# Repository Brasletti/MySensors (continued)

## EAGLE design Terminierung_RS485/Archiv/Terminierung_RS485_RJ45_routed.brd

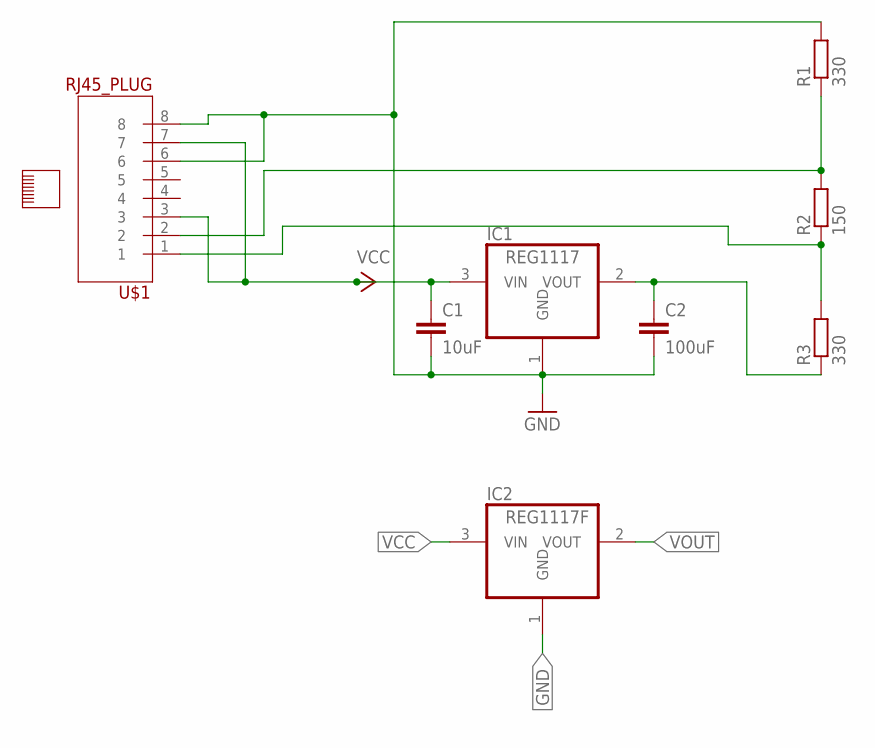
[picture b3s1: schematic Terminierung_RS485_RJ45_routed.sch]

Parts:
C1: 10uF; C0805K
C2: 100uF; C0805K
IC1: REG1117; SOT223
IC2: REG1117F; DD-3
R1, R3: 330; R0805
R2: 150; R0805
U$1: RJ45_PLUG

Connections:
GND: C1.2, C2.2, IC1.1 (GND), IC2.1 (GND), R1.2, U$1.6, U$1.8
unnamed: R1.1, R2.2, U$1.2
unnamed: R2.1, R3.2, U$1.1
VCC: C1.1, IC1.3 (VIN), IC2.3 (VIN), U$1.3, U$1.7
VOUT: C2.1, IC1.2 (VOUT), IC2.2 (VOUT), R3.1

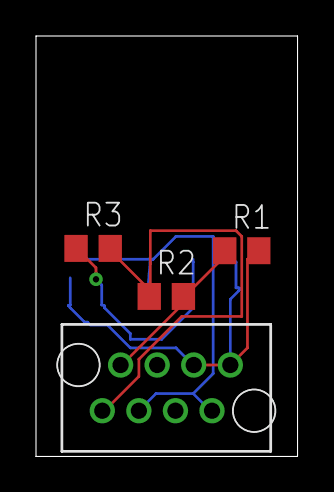
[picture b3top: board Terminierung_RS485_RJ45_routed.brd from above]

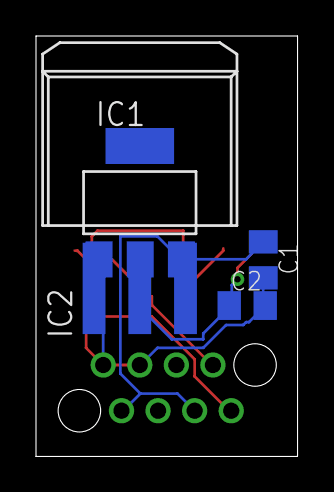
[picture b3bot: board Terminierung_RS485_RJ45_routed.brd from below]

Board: 2 copper layers, 14.5 x 23.4 mm, 8 parts (4 on the bottom side), 5 nets.

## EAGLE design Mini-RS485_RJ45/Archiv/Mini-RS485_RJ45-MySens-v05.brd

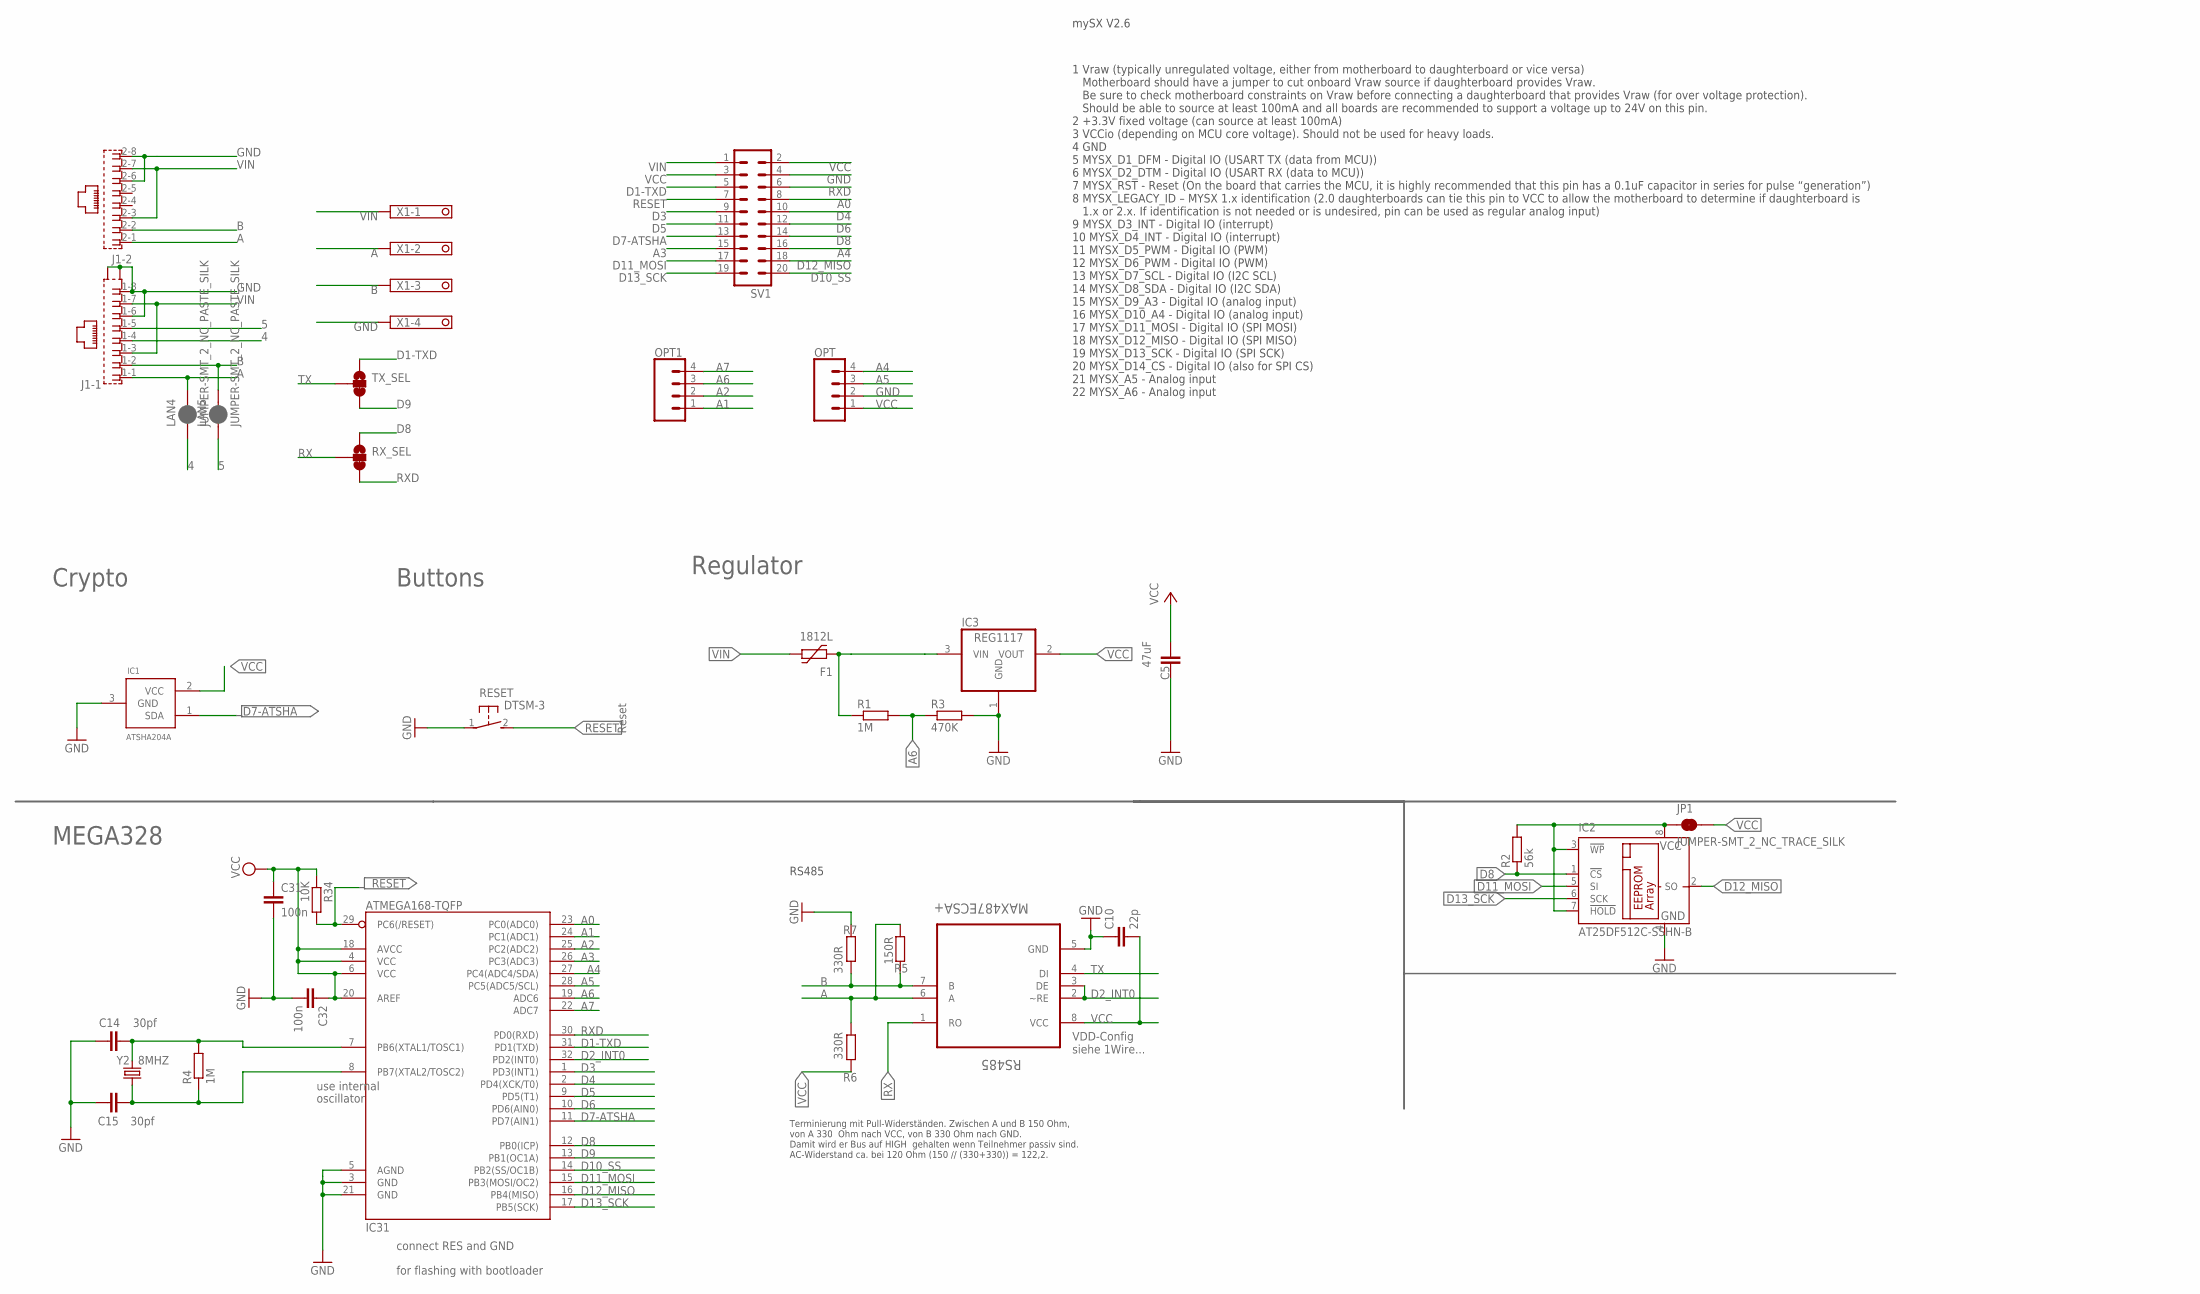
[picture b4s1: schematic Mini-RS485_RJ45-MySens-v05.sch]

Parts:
C5: 47uF; C1210
C10: 22p; C0805
C14, C15: 30pf; 0805
C31, C32: 100n; C0805
F1: 1812L
IC1: ATSHA204A; SOT23
IC2: AT25DF512C-SSHN-B; SO-08
IC3: REG1117; SOT223
IC31: ATMEGA168-TQFP; TQFP32-08
J1: RJ45_2X_NARROW_SHILDPINS
JP1: JUMPER-SMT_2_NC_TRACE_SILK; SMT-JUMPER_2_NC_TRACE_SILK
LAN4, LAN5: JUMPER-SMT_2_NC_PASTE_SILK; SMT-JUMPER_2_NC_PASTE_SILK
OPT, OPT1: CONN_04; 1X04
R1, R4: 1M; M0805
R2: 56k; M0805
R3: 470K; R0805
R5: 150R; R0805
R6, R7: 330R; R0805
R34: 10K; R0805
RESET: DTSM-3
RS485: MAX487ECSA+; SOIC127P600X175-8N
RX_SEL: JUMPER-SMT_3_1-NC_TRACE_SILK; SMT-JUMPER_3_1-NC_TRACE_SILK
SV1: MA10-2
TX_SEL: JUMPER-SMT_3_1-NC_TRACE_SILK; SMT-JUMPER_3_1-NC_TRACE_SILK
X1: 1751264
Y2: 8MHZ; CRYSTAL-TXC-7A

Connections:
4: J1.1-4 (4), LAN4.1
5: J1.1-5 (5), LAN5.1
A: J1.1-1 (1), J1.2-1 (1), LAN4.2, R5.1, R6.2, RS485.6 (A), X1.2
A0: IC31.23 (PC0(ADC0)), SV1.8
A1: IC31.24 (PC1(ADC1)), OPT1.1
A2: IC31.25 (PC2(ADC2)), OPT1.2
A3: IC31.26 (PC3(ADC3)), SV1.15
A4: IC31.27 (PC4(ADC4/SDA)), OPT.4, SV1.16
A5: IC31.28 (PC5(ADC5/SCL)), OPT.3
A6: IC31.19 (ADC6), OPT1.3, R1.2, R3.1
A7: IC31.22 (ADC7), OPT1.4
B: J1.1-2 (2), J1.2-2 (2), LAN5.2, R5.2, R7.1, RS485.7 (B), X1.3
D1-TXD: IC31.31 (PD1(TXD)), SV1.5, TX_SEL.1
D2_INT0: IC31.32 (PD2(INT0)), RS485.2 (~RE), RS485.3 (DE)
D3: IC31.1 (PD3(INT1)), SV1.9
D4: IC31.2 (PD4(XCK/T0)), SV1.10
D5: IC31.9 (PD5(T1)), SV1.11
D6: IC31.10 (PD6(AIN0)), SV1.12
D7-ATSHA: IC1.1 (SDA), IC31.11 (PD7(AIN1)), SV1.13
D8: IC2.1 (!CS), IC31.12 (PB0(ICP)), R2.1, RX_SEL.1, SV1.14
D9: IC31.13 (PB1(OC1A)), TX_SEL.3
D10_SS: IC31.14 (PB2(SS/OC1B)), SV1.20
D11_MOSI: IC2.5 (SI), IC31.15 (PB3(MOSI/OC2)), SV1.17
D12_MISO: IC2.2 (SO), IC31.16 (PB4(MISO)), SV1.18
D13_SCK: IC2.6 (SCK), IC31.17 (PB5(SCK)), SV1.19
GND: C5.1, C10.1, C14.1, C15.1, C31.2, C32.2, IC1.3 (GND), IC2.4 (GND), IC3.1 (GND), IC31.3 (GND), IC31.5 (AGND), IC31.21 (GND), J1.1-6 (6), J1.1-8 (8), J1.2-6 (6), J1.2-8 (8), J1.G1 (S1), J1.G3 (S2), OPT.2, R3.2, R7.2, RESET.1, RS485.5 (GND), SV1.4, X1.4
unnamed: C14.2, IC31.7 (PB6(XTAL1/TOSC1)), R4.2, Y2.P$2 (2)
unnamed: C15.2, IC31.8 (PB7(XTAL2/TOSC2)), R4.1, Y2.P$1 (1)
RESET: IC31.29 (PC6(/RESET)), R34.2, RESET.2, SV1.7
RX: RS485.1 (RO), RX_SEL.2
RXD: IC31.30 (PD0(RXD)), RX_SEL.3, SV1.6
TX: RS485.4 (DI), TX_SEL.2
VCC: C5.2, C10.2, C31.1, C32.1, IC1.2 (VCC), IC3.2 (VOUT), IC31.4 (VCC), IC31.6 (VCC), IC31.18 (AVCC), IC31.20 (AREF), JP1.2, OPT.1, R6.1, R34.1, RS485.8 (VCC), SV1.2, SV1.3
VCC1: IC2.3 (!WP), IC2.7 (!HOLD), IC2.8 (VCC), JP1.1, R2.2
VIN: F1.P$2 (2), J1.1-3 (3), J1.1-7 (7), J1.2-3 (3), J1.2-7 (7), SV1.1, X1.1
VIN-FUSED: F1.P$1 (1), IC3.3 (VIN), R1.1

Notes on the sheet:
MEGA328
use internal
oscillator
connect RES and GND
for flashing with bootloader
Reset
Crypto
Buttons
Regulator
RS485
VDD-Config siehe 1Wire...
Terminierung mit Pull-Widerständen. Zwischen A und B 150 Ohm, von A 330 Ohm nach VCC, von B 330 Ohm nach GND. Damit wird er Bus auf HIGH gehalten wenn Teilnehmer passiv sind. AC-Widerstand ca. bei 120 Ohm (150 // (330+330)) = 122,2.
1 Vraw (typically unregulated voltage, either from motherboard to daughterboard or vice versa) Motherboard should have a jumper to cut onboard Vraw source if daughterboard provides Vraw. Be sure to check motherboard constraints on Vraw before connecting a daughterboard that provides Vraw (for over 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
mySX V2.6

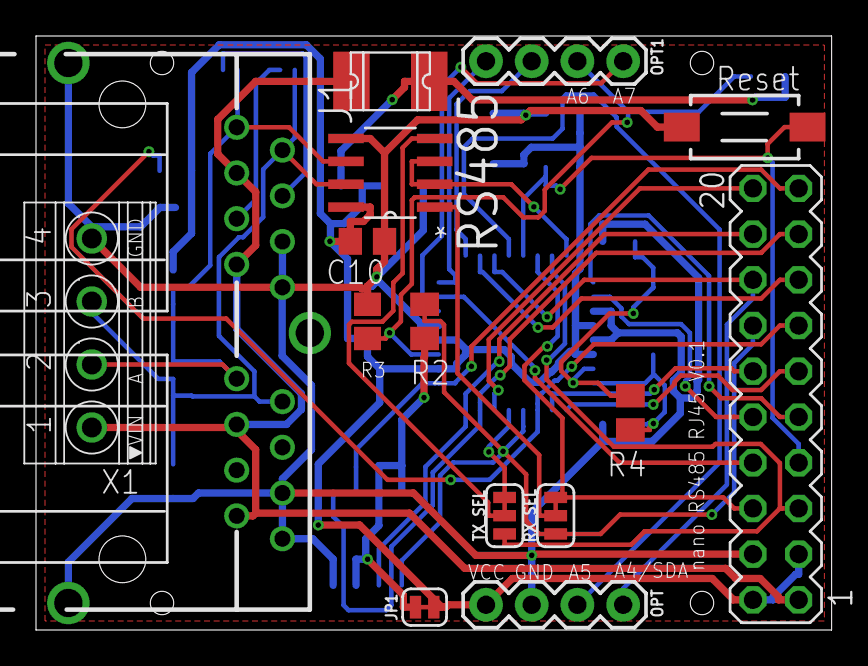
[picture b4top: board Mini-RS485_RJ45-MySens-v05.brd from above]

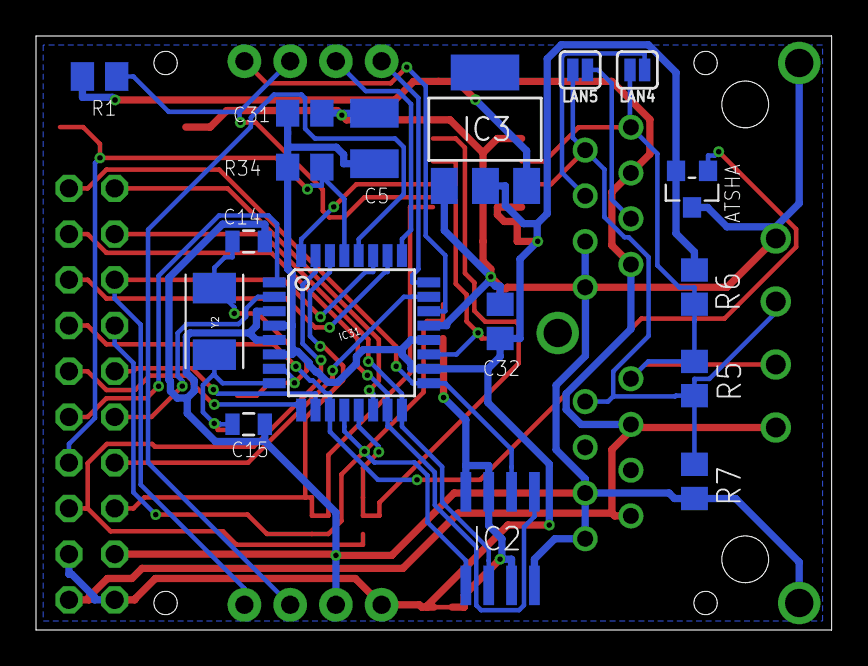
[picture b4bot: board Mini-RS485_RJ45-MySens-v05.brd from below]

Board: 2 copper layers, 44.2 x 33.0 mm, 32 parts (17 on the bottom side), 36 nets.

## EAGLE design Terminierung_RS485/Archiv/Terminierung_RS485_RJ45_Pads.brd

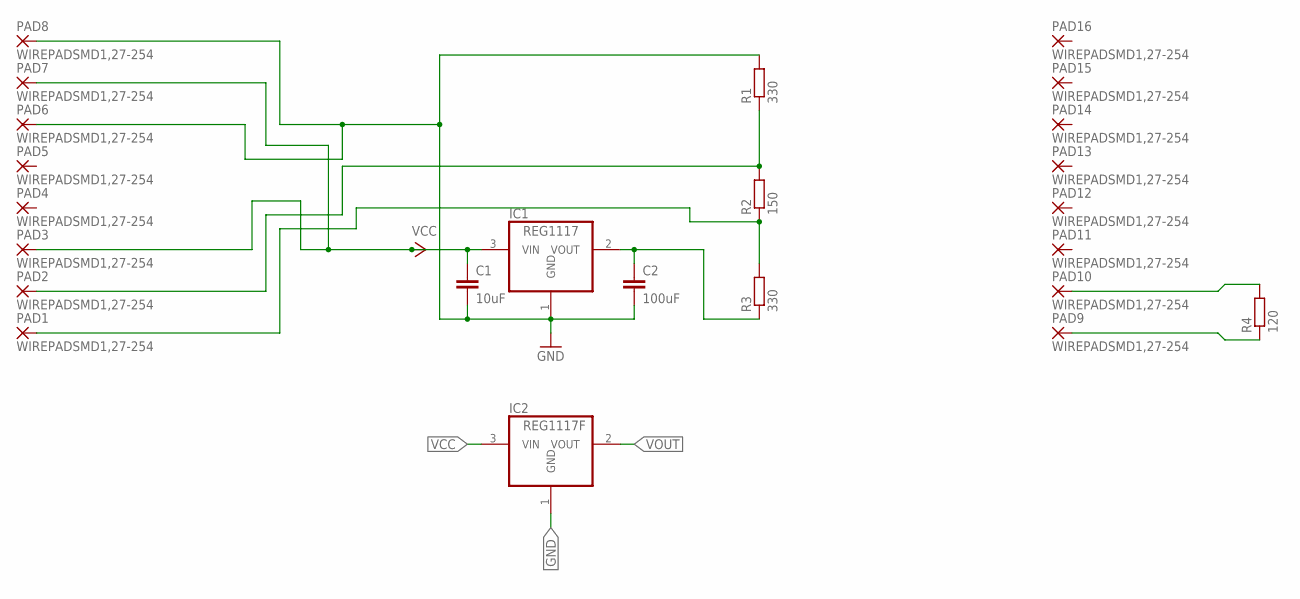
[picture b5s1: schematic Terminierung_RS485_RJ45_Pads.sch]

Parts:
C1: 10uF; C0805K
C2: 100uF; C0805K
IC1: REG1117; SOT223
IC2: REG1117F; DD-3
PAD1, PAD2, PAD3, PAD4, PAD5, PAD6, PAD7, PAD8, PAD9, PAD10, PAD11, PAD12, PAD13, PAD14, PAD15, PAD16: WIREPADSMD1,27-254; SMD1,27-2,54
R1, R3: 330; R0805
R2: 150; R0805
R4: 120; R0805

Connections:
GND: C1.2, C2.2, IC1.1 (GND), IC2.1 (GND), PAD6.1, PAD8.1, R1.2
unnamed: PAD10.1, R4.2
unnamed: PAD9.1, R4.1
unnamed: PAD2.1, R1.1, R2.2
unnamed: PAD1.1, R2.1, R3.2
VCC: C1.1, IC1.3 (VIN), IC2.3 (VIN), PAD3.1, PAD7.1
VOUT: C2.1, IC1.2 (VOUT), IC2.2 (VOUT), R3.1

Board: 2 copper layers, 24 parts (12 on the bottom side), 7 nets, no tracks yet.

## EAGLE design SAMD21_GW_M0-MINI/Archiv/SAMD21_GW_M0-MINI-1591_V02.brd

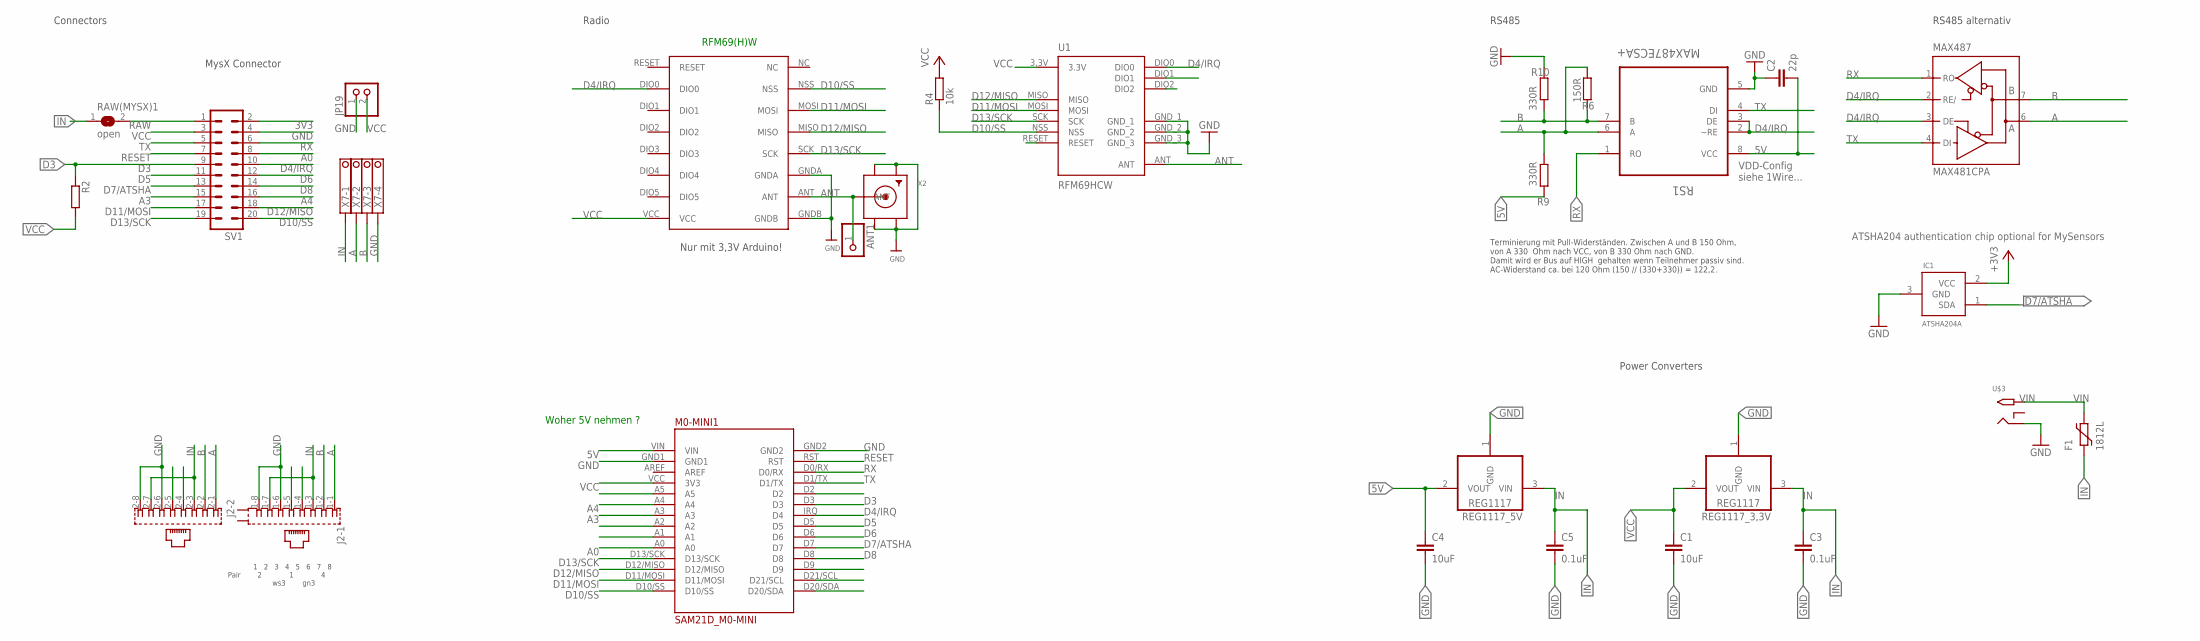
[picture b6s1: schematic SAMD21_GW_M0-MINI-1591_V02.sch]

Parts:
ANT1: PINHD-1X1; 1X01
C1, C4: 10uF; C1210
C2: 22p; C0805
C3, C5: 0.1uF; C1206
F1: 1812L
IC1: ATSHA204A; SOT23
J2: 557570-1
JP19: PINHD-1X2; 1X02
M0-MINI1: SAM21D_M0-MINI; SAMD21_M0-MINI
MAX487: MAX481CPA; DIL08
R2: R-EU_R0805; R0805
R4: 10k; M0805
R6: 150R; R0805
R9, R10: 330R; R0805
RAW(MYSX)1: open; SJ
REG1117_3,3V, REG1117_5V: REG1117; SOT223
RFM69W: RFM69HW; RFM
RS1: MAX487ECSA+; SOIC127P600X175-8N
SV1: MA10-2
U1: RFM69HCW; RFM69HCW-XXXS2
U$3: 2.1MMJACKTHM; PJ-102A
X2: SMACONNECTOR_EDGE; SMA_EDGELAUNCH
X7: 1751264

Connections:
3V3: SV1.2
5V: C2.2, C4.1, M0-MINI1.VIN, R9.1, REG1117_5V.2 (VOUT), RS1.8 (VCC)
A: J2.1-1 (1), J2.2-1 (1), MAX487.6 (A), R6.1, R9.2, RS1.6 (A), X7.2
A0: M0-MINI1.A0, SV1.8
A3: M0-MINI1.A3, SV1.15
A4: M0-MINI1.A4, SV1.16
ANT: ANT1.1, RFM69W.ANT, U1.ANT, X2.P (ANT)
B: J2.1-2 (2), J2.2-2 (2), MAX487.7 (B), R6.2, R10.1, RS1.7 (B), X7.3
D3: M0-MINI1.D3, R2.1, SV1.9
D4/IRQ: M0-MINI1.IRQ (D4), RFM69W.DIO0, RS1.2 (~RE), RS1.3 (DE), SV1.10, U1.DIO0
D5: M0-MINI1.D5, SV1.11
D6: M0-MINI1.D6, SV1.12
D7/ATSHA: IC1.1 (SDA), M0-MINI1.D7, SV1.13
D8: M0-MINI1.D8, SV1.14
D10/SS: M0-MINI1.D10/SS, R4.1, RFM69W.NSS, SV1.20, U1.NSS
D11/MOSI: M0-MINI1.D11/MOSI, RFM69W.MOSI, SV1.17, U1.MOSI
D12/MISO: M0-MINI1.D12/MISO, RFM69W.MISO, SV1.18, U1.MISO
D13/SCK: M0-MINI1.D13/SCK, RFM69W.SCK, SV1.19, U1.SCK
GND: C1.2, C2.1, C3.2, C4.2, C5.2, IC1.3 (GND), J2.1-6 (6), J2.1-8 (8), J2.2-6 (6), J2.2-8 (8), JP19.1, M0-MINI1.GND1, M0-MINI1.GND2, MAX487.5 (GND), R10.2, REG1117_3,3V.1 (GND), REG1117_5V.1 (GND), RFM69W.GNDA, RFM69W.GNDB, RS1.5 (GND), SV1.4, U1.GND_1, U1.GND_2, U1.GND_3, U$3.RING, X2.GND@1 (GND4), X2.GND@2 (GND3), X2.GND@3 (GND2), X2.GND@4 (GND1), X7.4
IN: C3.1, C5.1, F1.P$1 (1), J2.1-3 (3), J2.1-7 (7), J2.2-3 (3), J2.2-7 (7), RAW(MYSX)1.1, REG1117_3,3V.3 (VIN), REG1117_5V.3 (VIN), X7.1
RAW: RAW(MYSX)1.2, SV1.1
RESET: M0-MINI1.RST, SV1.7
RX: M0-MINI1.D0/RX, RS1.1 (RO), SV1.6
TX: M0-MINI1.D1/TX, RS1.4 (DI), SV1.5
VCC: C1.1, IC1.2 (VCC), JP19.2, M0-MINI1.VCC (3V3), MAX487.8 (VCC), R2.2, R4.2, REG1117_3,3V.2 (VOUT), RFM69W.VCC, SV1.3, U1.3.3V
VIN: F1.P$2 (2), U$3.TIP

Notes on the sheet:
RFM69(H)W
Nur mit 3,3V Arduino!
Radio
1 2 3 4 5 6 7 8 Pair 2 1 4 ws3 gn3
Power Converters
ATSHA204 authentication chip optional for MySensors
RS485
VDD-Config siehe 1Wire...
Terminierung mit Pull-Widerständen. Zwischen A und B 150 Ohm, von A 330 Ohm nach VCC, von B 330 Ohm nach GND. Damit wird er Bus auf HIGH gehalten wenn Teilnehmer passiv sind. AC-Widerstand ca. bei 120 Ohm (150 // (330+330)) = 122,2.
RS485 alternativ
Connectors
MysX Connector
Woher 5V nehmen ?

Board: 2 copper layers, 28 parts (6 on the bottom side), 25 nets, no tracks yet.

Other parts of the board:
U$2: 1591XXA

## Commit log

2018-01-06 Create LICENSE
2018-01-06 V.0.1
2018-01-06 For Hammond 1591
2018-01-07 V02/V03
2018-01-07 RJ45 Terminator
2018-01-07 RJ45 with Pads
2018-01-07 V.0.4
2018-04-04 Eagle V7
2018-04-07 Fusbit_Doc
2018-04-07 Delete
